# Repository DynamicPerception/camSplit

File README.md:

camSplit Board
==============

The camSplit board is the heart of the [MUX-4 4-Way Isolated Camera Splitter](http://dynamicperception.com/products/mux-4-camera-splitter) sold by Dynamic Perception LLC.

Not limited to controlling cameras, the camSplit provides a safe, and isolated way to multiply any two trigger outputs out to four separate devices, even if those devices have wildly different voltages (from 1.5V to 80V DC).  True optical isolation on every port means that different devices can safely react to the same control signal - allowing you to synchronize lights, cameras, and more.

Key Features 
------------

- Complete optical isolation between all cameras and control inputs 
- Can work with isolated intervalometer outputs (like the MX2) 
- Runs on 2x AAA batteries, will last many months between changes 
- Manual triggering of the shutter/focus lines via pushbuttons 
- Can be daisy-chained (feed one output to the input of another) 

License and Copyright
---------------------

camSplit and the MUX-4 are Copyright (c) 2012-2013 Dynamic Perception LLC.

All files shared under the Creative Commons Attibution-Share-Alike 3.0 License.

camSplit and MUX-4 names are trademarks of Dynamic Perception LLC.

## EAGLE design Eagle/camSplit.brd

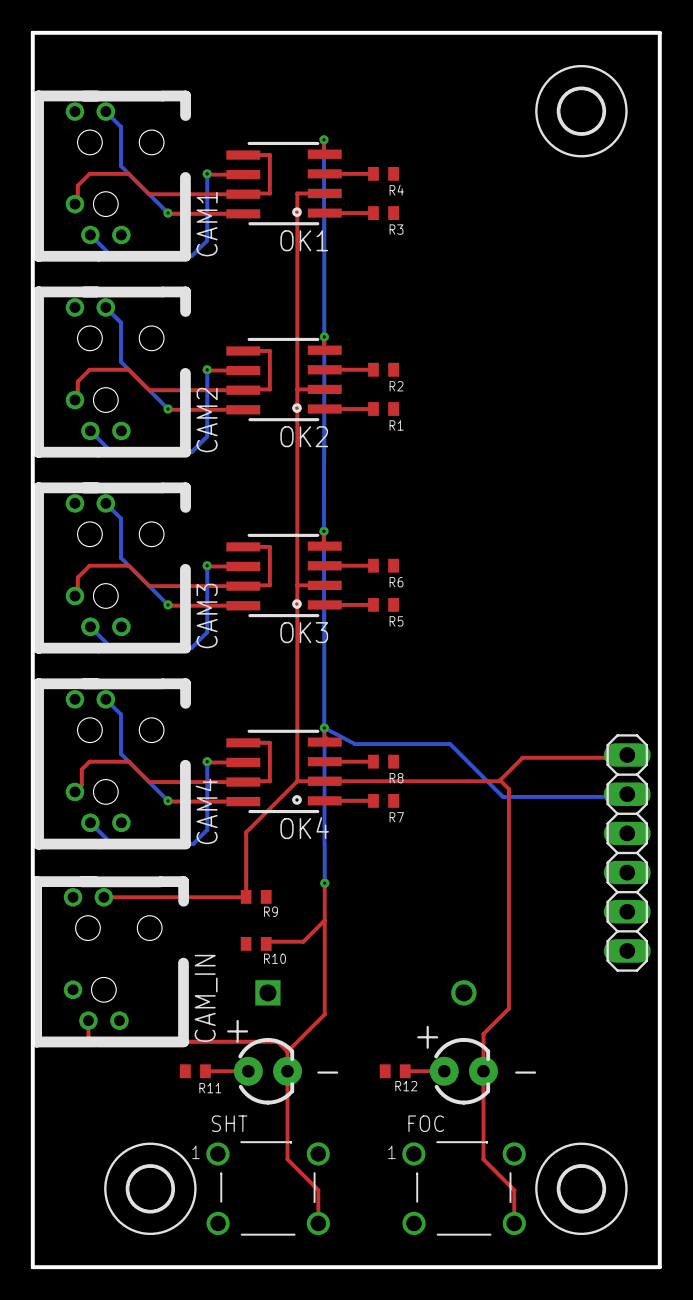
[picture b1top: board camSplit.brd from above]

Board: 2 copper layers, 40.6 x 80.0 mm, 30 parts (1 on the bottom side), 26 nets.

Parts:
2XAAA: 12BH423-GR
CAM1, CAM2, CAM3, CAM4: 161-2508-EXTHRU-HOLE-PCB-RA; PCB-HORIZ
CAM_IN: 161-2508-EXTHRU-HOLE-PCB-RA; PCB-HORIZ
FOC: SKHHCWA010; SKHH
H1, H2, H3: MOUNT-HOLE2.8; 2,8
JP1: conn; 1X06
LFOC: LED3MM
LSHT: LED3MM
OK1, OK2, OK3, OK4: ACPL-227; SOIC8
R1, R2, R3, R4, R5, R6, R7, R8, R11, R12: 90; R0402
R9, R10: 150k; R0402
SHT: SKHHCWA010; SKHH

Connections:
3V: 2XAAA.POS, JP1.1, JP1.3, R1.1, R2.1, R3.1, R4.1, R5.1, R6.1, R7.1, R8.1, R9.2, R10.1, R11.1, R12.1
CAM_FOC: CAM_IN.4, FOC.4, JP1.6, LFOC.K, OK1.2, OK2.2, OK3.2, OK4.2, R9.1
CAM_SHT: CAM_IN.2, JP1.5, LSHT.K, OK1.4, OK2.4, OK3.4, OK4.4, R10.2, SHT.4
COM_OUT1: CAM1.1, OK1.5, OK1.7
COM_OUT2: CAM2.1, OK2.5, OK2.7
COM_OUT3: CAM3.1, OK3.5, OK3.7
COM_OUT4: CAM4.1, OK4.5, OK4.7
FOC_OUT1: CAM1.4, OK1.8
FOC_OUT2: CAM2.4, OK2.8
FOC_OUT3: CAM3.4, OK3.8
FOC_OUT4: CAM4.4, OK4.8
GND: 2XAAA.NEG, CAM_IN.1, FOC.1, JP1.2, JP1.4, SHT.1
unnamed: OK1.1, R3.2
unnamed: OK2.1, R1.2
unnamed: OK1.3, R4.2
unnamed: OK2.3, R2.2
unnamed: OK3.1, R5.2
unnamed: OK3.3, R6.2
unnamed: OK4.1, R7.2
unnamed: OK4.3, R8.2
unnamed: LSHT.A, R11.2
unnamed: LFOC.A, R12.2
SHUT_OUT1: CAM1.2, OK1.6
SHUT_OUT2: CAM2.2, OK2.6
SHUT_OUT3: CAM3.2, OK3.6
SHUT_OUT4: CAM4.2, OK4.6

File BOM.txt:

Partlist

Exported from camSplit.sch at 3/28/13 10:39 AM

EAGLE Version 6.1.0 Copyright (c) 1988-2012 CadSoft

Assembly variant: 

Part     Value                       Device                      Package    Library               Sheet

2XAAA                                12BH423-GR                  12BH423-GR eagle-plastic-devices 1
CAM1     161-2508-EXTHRU-HOLE-PCB-RA 161-2508-EXTHRU-HOLE-PCB-RA PCB-HORIZ  kobiconn-161-2508-ex  1
CAM2     161-2508-EXTHRU-HOLE-PCB-RA 161-2508-EXTHRU-HOLE-PCB-RA PCB-HORIZ  kobiconn-161-2508-ex  1
CAM3     161-2508-EXTHRU-HOLE-PCB-RA 161-2508-EXTHRU-HOLE-PCB-RA PCB-HORIZ  kobiconn-161-2508-ex  1
CAM4     161-2508-EXTHRU-HOLE-PCB-RA 161-2508-EXTHRU-HOLE-PCB-RA PCB-HORIZ  kobiconn-161-2508-ex  1
CAM_IN   161-2508-EXTHRU-HOLE-PCB-RA 161-2508-EXTHRU-HOLE-PCB-RA PCB-HORIZ  kobiconn-161-2508-ex  1
FOC      SKHHCWA010                  SKHH                        SKHH       alps                  1
JP1      conn                        PINHD-1X6                   1X06       pinhead               1
LFOC                                 LED3MM                      LED3MM     SparkFun              1
LSHT                                 LED3MM                      LED3MM     SparkFun              1
OK1      ACPL-227                    ACPL-227                    SOIC8      avago-opto            1
OK2      ACPL-227                    ACPL-227                    SOIC8      avago-opto            1
OK3      ACPL-227                    ACPL-227                    SOIC8      avago-opto            1
OK4      ACPL-227                    ACPL-227                    SOIC8      avago-opto            1
R1       90                          R-US_R0402                  R0402      resistor              1
R2       90                          R-US_R0402                  R0402      resistor              1
R3       90                          R-US_R0402                  R0402      resistor              1
R4       90                          R-US_R0402                  R0402      resistor              1
R5       90                          R-US_R0402                  R0402      resistor              1
R6       90                          R-US_R0402                  R0402      resistor              1
R7       90                          R-US_R0402                  R0402      resistor              1
R8       90                          R-US_R0402                  R0402      resistor              1
R9       150k                        R-US_R0402                  R0402      resistor              1
R10      150k                        R-US_R0402                  R0402      resistor              1
R11      90                          R-US_R0402                  R0402      resistor              1
R12      90                          R-US_R0402                  R0402      resistor              1
SHT      SKHHCWA010                  SKHH                        SKHH       alps                  1

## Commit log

2013-03-28 * Added files
